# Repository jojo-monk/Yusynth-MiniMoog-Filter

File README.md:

# Yusynth-MiniMoog-Filter
Adaptation du Yusynth [MiniMoog Filter](http://yusynth.net/Modular/index_en.html) au format Eurorack

testé et fonctionnel.

petit défaut esthetique : sérigraphie un peu trop petite et trop proche des boutons.

[Build document](https://htmlpreview.github.io/?https://github.com/jojo-monk/Yusynth-MiniMoog-Filter/blob/main/ibom.html)

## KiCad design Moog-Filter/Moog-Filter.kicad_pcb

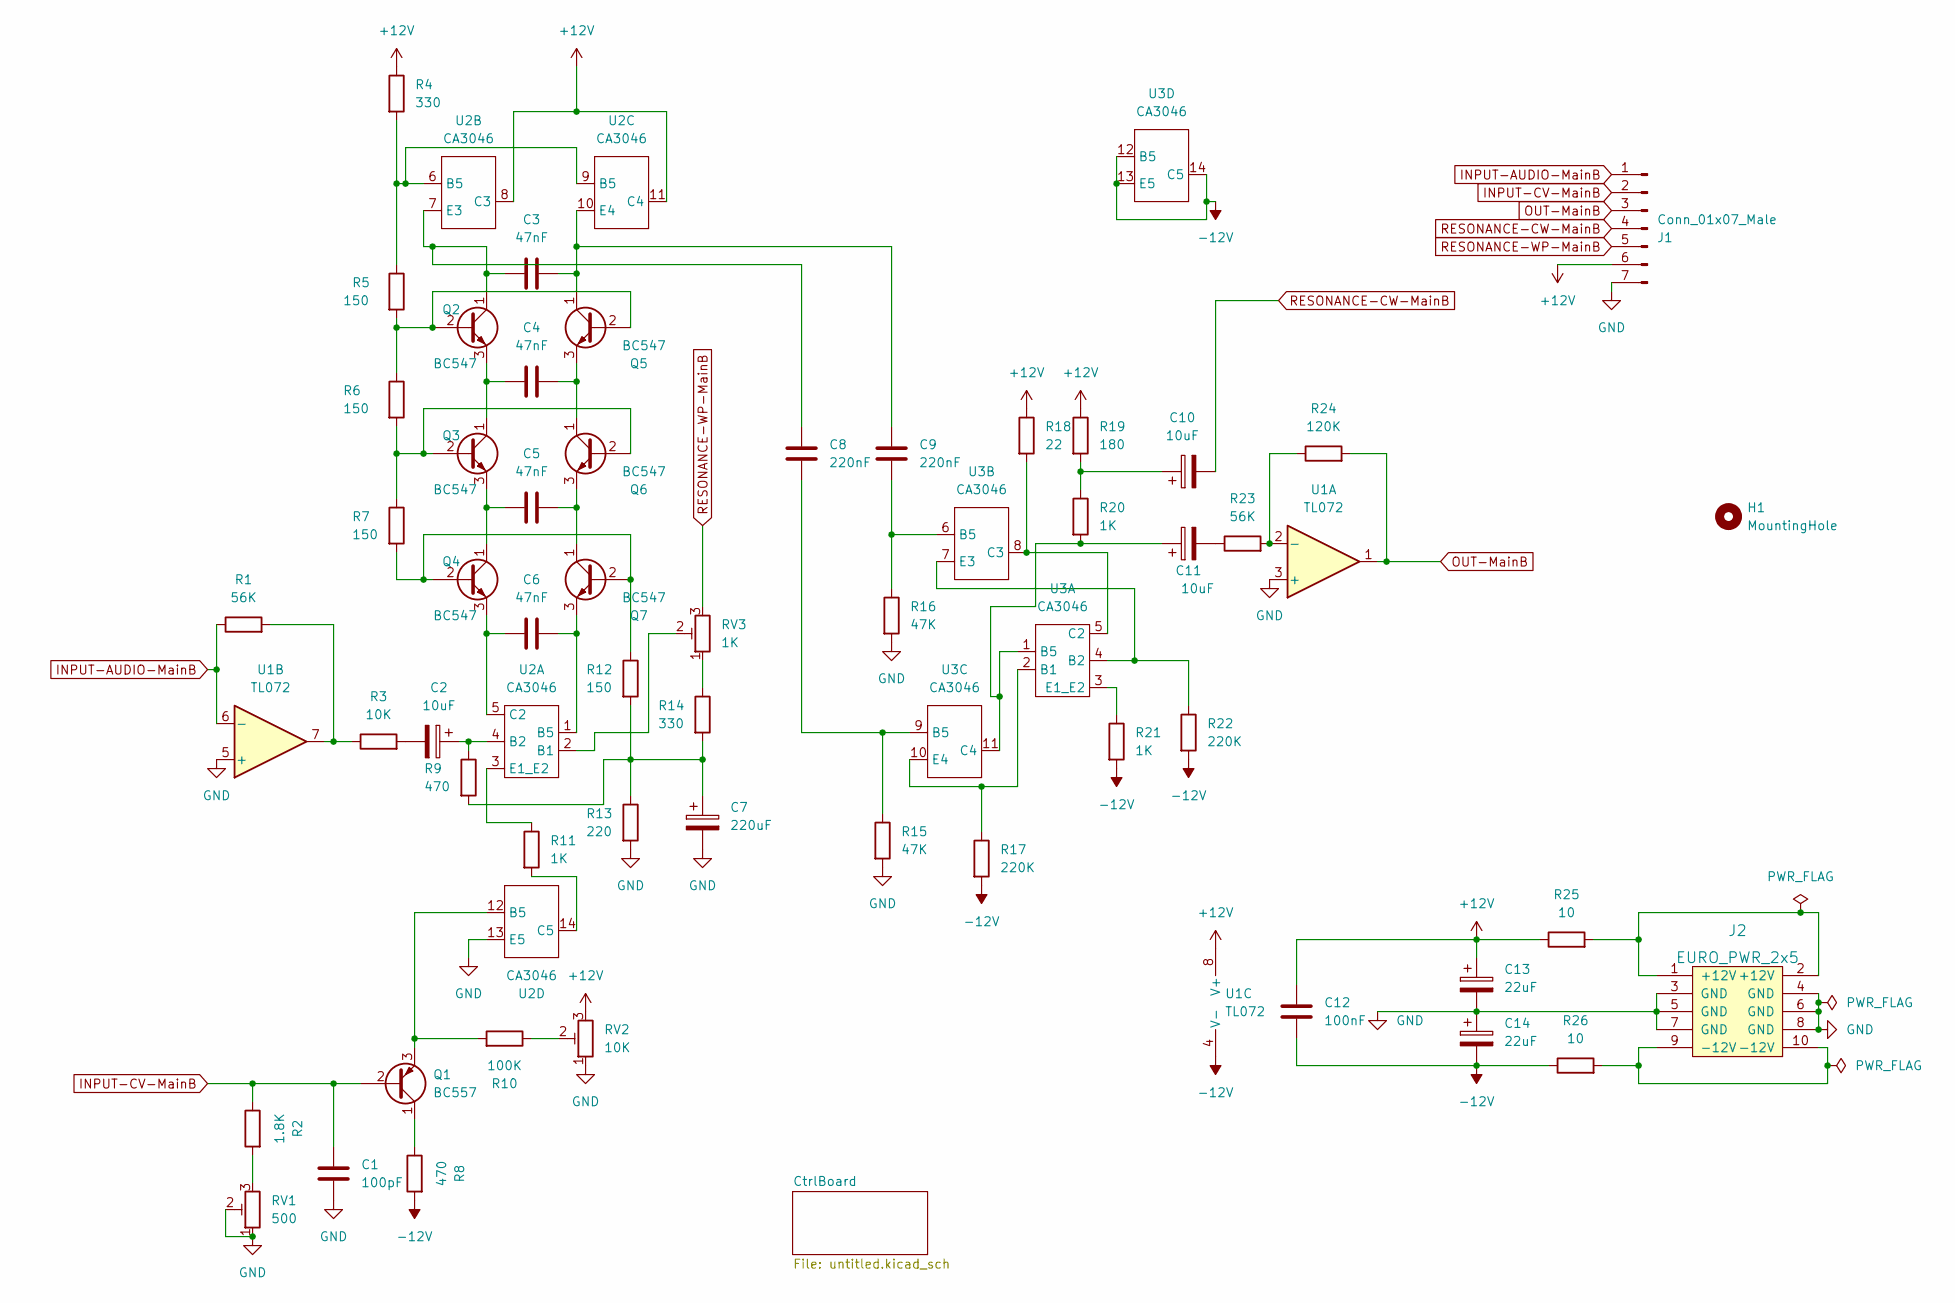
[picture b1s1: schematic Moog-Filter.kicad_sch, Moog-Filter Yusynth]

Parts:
C1: 100pF; C_Rect_L7.0mm_W3.5mm_P5.00mm
C2, C10, C11: 10uF; CP_Radial_D5.0mm_P2.00mm
C3, C4, C5, C6: 47nF; C_Rect_L7.0mm_W3.5mm_P5.00mm
C7: 220uF; CP_Radial_D8.0mm_P3.50mm
C8, C9: 220nF; C_Rect_L7.0mm_W3.5mm_P5.00mm
C12: 100nF; C_Rect_L7.0mm_W3.5mm_P5.00mm
C13, C14: 22uF; CP_Radial_D5.0mm_P2.00mm
H1: MountingHole; MountingHole_3.2mm_M3
J1: Conn_01x07_Male; PinHeader_1x07_P2.54mm_Vertical
J2: EURO_PWR_2x5; Eurorack_power_header
Q1: BC557; TO-92_HandSolder
Q2, Q3, Q4, Q5, Q6, Q7: BC547; TO-92_HandSolder
R1, R23: 56K; R_Axial_DIN0207_L6.3mm_D2.5mm_P2.54mm_Vertical
R2: 1.8K; R_Axial_DIN0207_L6.3mm_D2.5mm_P2.54mm_Vertical
R3: 10K; R_Axial_DIN0207_L6.3mm_D2.5mm_P2.54mm_Vertical
R4, R14: 330; R_Axial_DIN0207_L6.3mm_D2.5mm_P2.54mm_Vertical
R5, R6, R7, R12: 150; R_Axial_DIN0207_L6.3mm_D2.5mm_P2.54mm_Vertical
R8, R9: 470; R_Axial_DIN0207_L6.3mm_D2.5mm_P2.54mm_Vertical
R10: 100K; R_Axial_DIN0207_L6.3mm_D2.5mm_P2.54mm_Vertical
R11, R20, R21: 1K; R_Axial_DIN0207_L6.3mm_D2.5mm_P2.54mm_Vertical
R13: 220; R_Axial_DIN0207_L6.3mm_D2.5mm_P2.54mm_Vertical
R15, R16: 47K; R_Axial_DIN0207_L6.3mm_D2.5mm_P2.54mm_Vertical
R17, R22: 220K; R_Axial_DIN0207_L6.3mm_D2.5mm_P2.54mm_Vertical
R18: 22; R_Axial_DIN0207_L6.3mm_D2.5mm_P2.54mm_Vertical
R19: 180; R_Axial_DIN0207_L6.3mm_D2.5mm_P2.54mm_Vertical
R24: 120K; R_Axial_DIN0207_L6.3mm_D2.5mm_P2.54mm_Vertical
R25, R26: 10; R_Axial_DIN0207_L6.3mm_D2.5mm_P2.54mm_Vertical
RV1: 500; Potentiometer_Bourns_3296W_Vertical
RV2: 10K; Potentiometer_Bourns_3296W_Vertical
RV3: 1K; Potentiometer_Bourns_3296W_Vertical
U1: TL072; DIP-8_W7.62mm_LongPads
U2, U3: CA3046; DIP-14_W7.62mm_LongPads

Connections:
+12V: C12.1, C13.1, J1.6, R4.1, R18.1, R19.1, R25.1, RV2.3, U1.8 (V+), U2.8 (C3), U2.11 (C4); also elsewhere on the board
-12V: C12.2, C14.2, R8.2, R17.2, R21.2, R22.2, R26.1, U1.4 (V-), U3.12 (B5), U3.13 (E5), U3.14 (C5)
GND: C1.2, C7.2, C13.2, C14.1, J1.7, J2.3 (GND), J2.4 (GND), J2.5 (GND), J2.6 (GND), J2.7 (GND), J2.8 (GND), R13.2, R15.2, R16.2, RV1.1, RV1.2, RV2.1, U1.3 (+), U1.5 (+), U2.13 (E5); also elsewhere on the board
INPUT-AUDIO-MainB: J1.1, R1.1, U1.6 (-)
INPUT-CV-MainB: C1.1, J1.2, Q1.2 (B), R2.1
unnamed: C2.1, R9.1, U2.4 (B2)
unnamed: C2.2, R3.2
unnamed: C3.1, C8.1, Q2.1 (C), U2.7 (E3)
unnamed: C3.2, C9.1, Q5.1 (C), U2.10 (E4)
unnamed: C4.1, Q2.3 (E), Q3.1 (C)
unnamed: C4.2, Q5.3 (E), Q6.1 (C)
unnamed: C5.1, Q3.3 (E), Q4.1 (C)
unnamed: C5.2, Q6.3 (E), Q7.1 (C)
unnamed: C6.1, Q4.3 (E), U2.5 (C2)
unnamed: C6.2, Q7.3 (E), U2.1 (B5)
unnamed: C7.1, R9.2, R12.2, R13.1, R14.2
unnamed: C8.2, R15.1, U3.9 (B5)
unnamed: C9.2, R16.1, U3.6 (B5)
unnamed: C10.1, R19.2, R20.1
unnamed: C11.1, R20.2, U3.1 (B5), U3.11 (C4)
unnamed: C11.2, R23.1
unnamed: J2.1 (+12V), J2.2 (+12V), R25.2
unnamed: J2.9 (-12V), J2.10 (-12V), R26.2
unnamed: Q1.1 (C), R8.1
unnamed: Q1.3 (E), R10.2, U2.12 (B5)
unnamed: Q2.2 (B), Q5.2 (B), R5.2, R6.1
unnamed: Q3.2 (B), Q6.2 (B), R6.2, R7.1
unnamed: Q4.2 (B), Q7.2 (B), R7.2, R12.1
unnamed: R1.2, R3.1, U1.7
unnamed: R2.2, RV1.3
unnamed: R4.2, R5.1, U2.6 (B5), U2.9 (B5)
unnamed: R10.1, RV2.2
unnamed: R11.1, U2.3 (E1_E2)
unnamed: R11.2, U2.14 (C5)
unnamed: R14.1, RV3.1
unnamed: R17.1, U3.2 (B1), U3.10 (E4)
unnamed: R18.2, U3.5 (C2), U3.8 (C3)
unnamed: R21.1, U3.3 (E1_E2)
unnamed: R22.1, U3.4 (B2), U3.7 (E3)
unnamed: R23.2, R24.1, U1.2 (-)
unnamed: RV3.2, U2.2 (B1)
OUT-MainB: J1.3, R24.2, U1.1
RESONANCE-CW-MainB: C10.2, J1.4
RESONANCE-WP-MainB: J1.5, RV3.3

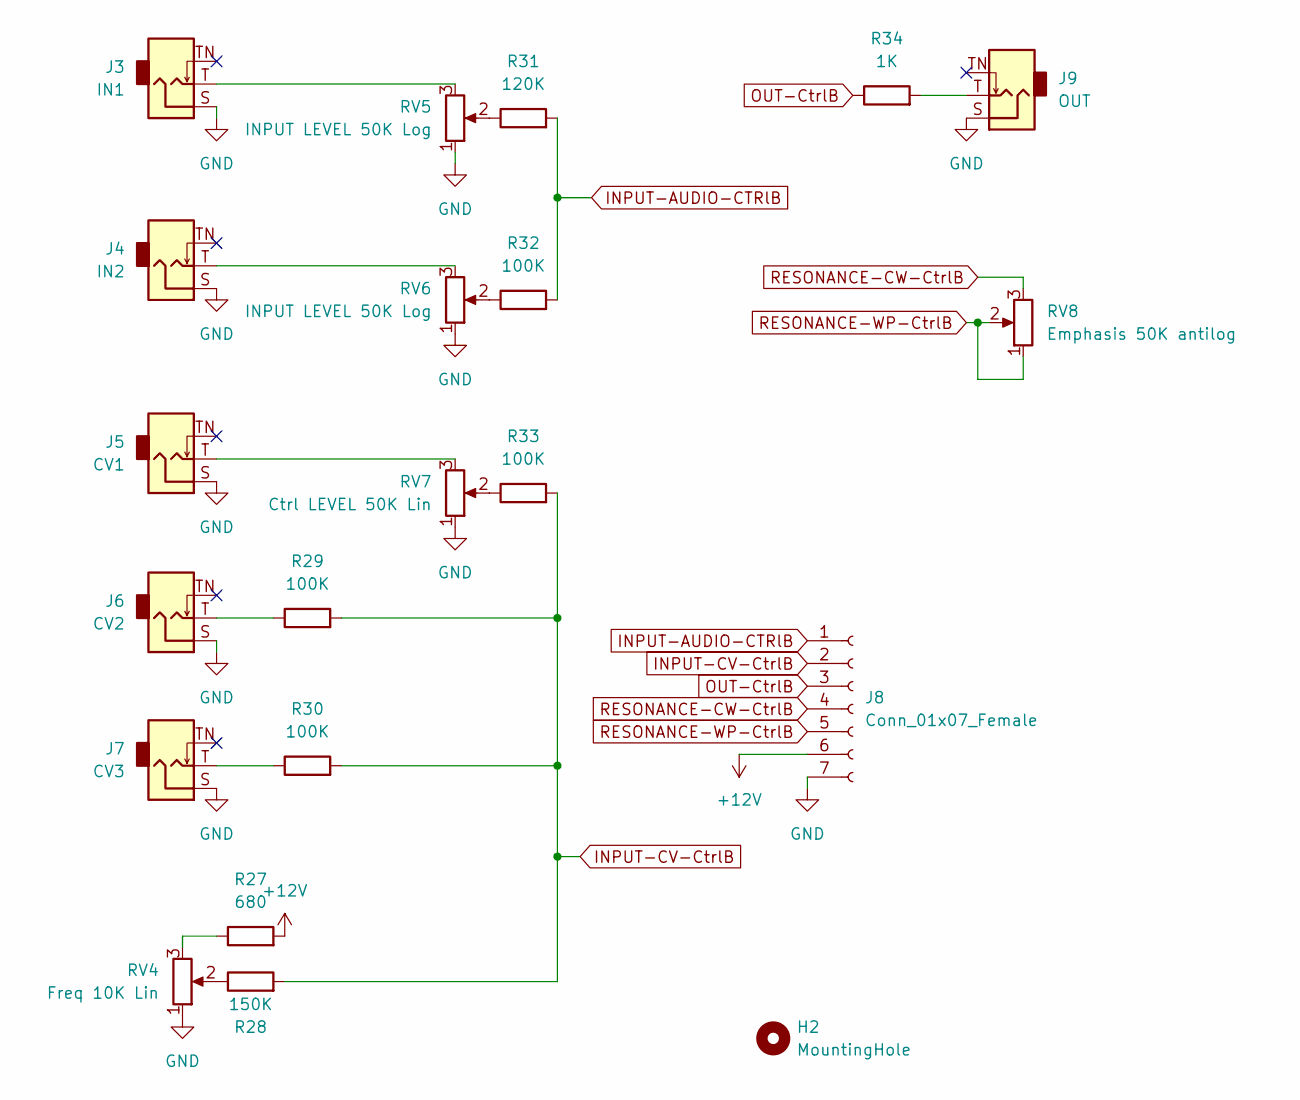
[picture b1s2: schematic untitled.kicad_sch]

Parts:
H2: MountingHole; MountingHole_3.2mm_M3
J3: IN1; Jack_3.5mm_QingPu_WQP-PJ398SM_Vertical
J4: IN2; Jack_3.5mm_QingPu_WQP-PJ398SM_Vertical
J5: CV1; Jack_3.5mm_QingPu_WQP-PJ398SM_Vertical
J6: CV2; Jack_3.5mm_QingPu_WQP-PJ398SM_Vertical
J7: CV3; Jack_3.5mm_QingPu_WQP-PJ398SM_Vertical
J8: Conn_01x07_Female; PinHeader_1x07_P2.54mm_Vertical
J9: OUT; Jack_3.5mm_QingPu_WQP-PJ398SM_Vertical
R27: 680; R_Axial_DIN0207_L6.3mm_D2.5mm_P2.54mm_Vertical
R28: 150K; R_Axial_DIN0207_L6.3mm_D2.5mm_P2.54mm_Vertical
R29, R30, R32, R33: 100K; R_Axial_DIN0207_L6.3mm_D2.5mm_P2.54mm_Vertical
R31: 120K; R_Axial_DIN0207_L6.3mm_D2.5mm_P2.54mm_Vertical
R34: 1K; R_Axial_DIN0207_L6.3mm_D2.5mm_P2.54mm_Vertical
RV4: Freq 10K Lin; Potentiometer_Alpha_RD901F-40-00D_Single_Vertical
RV5, RV6: INPUT LEVEL 50K Log; Potentiometer_Alpha_RD901F-40-00D_Single_Vertical
RV7: Ctrl LEVEL 50K Lin; Potentiometer_Alpha_RD901F-40-00D_Single_Vertical
RV8: Emphasis 50K antilog; Potentiometer_Alpha_RD901F-40-00D_Single_Vertical

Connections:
+12V: J8.6, R27.2; also elsewhere on the board
GND: J3.S, J4.S, J5.S, J6.S, J7.S, J8.7, J9.S, RV4.1, RV5.1, RV6.1, RV7.1; also elsewhere on the board
INPUT-AUDIO-CTRlB: J8.1, R31.2, R32.2
INPUT-CV-CtrlB: J8.2, R28.2, R29.2, R30.2, R33.2
unnamed: J3.T, RV5.3
unnamed: J4.T, RV6.3
unnamed: J5.T, RV7.3
unnamed: J6.T, R29.1
unnamed: J7.T, R30.1
unnamed: J9.T, R34.2
unnamed: R27.1, RV4.3
unnamed: R28.1, RV4.2
unnamed: R31.1, RV5.2
unnamed: R32.1, RV6.2
unnamed: R33.1, RV7.2
OUT-CtrlB: J8.3, R34.1
RESONANCE-CW-CtrlB: J8.4, RV8.3
RESONANCE-WP-CtrlB: J8.5, RV8.1, RV8.2

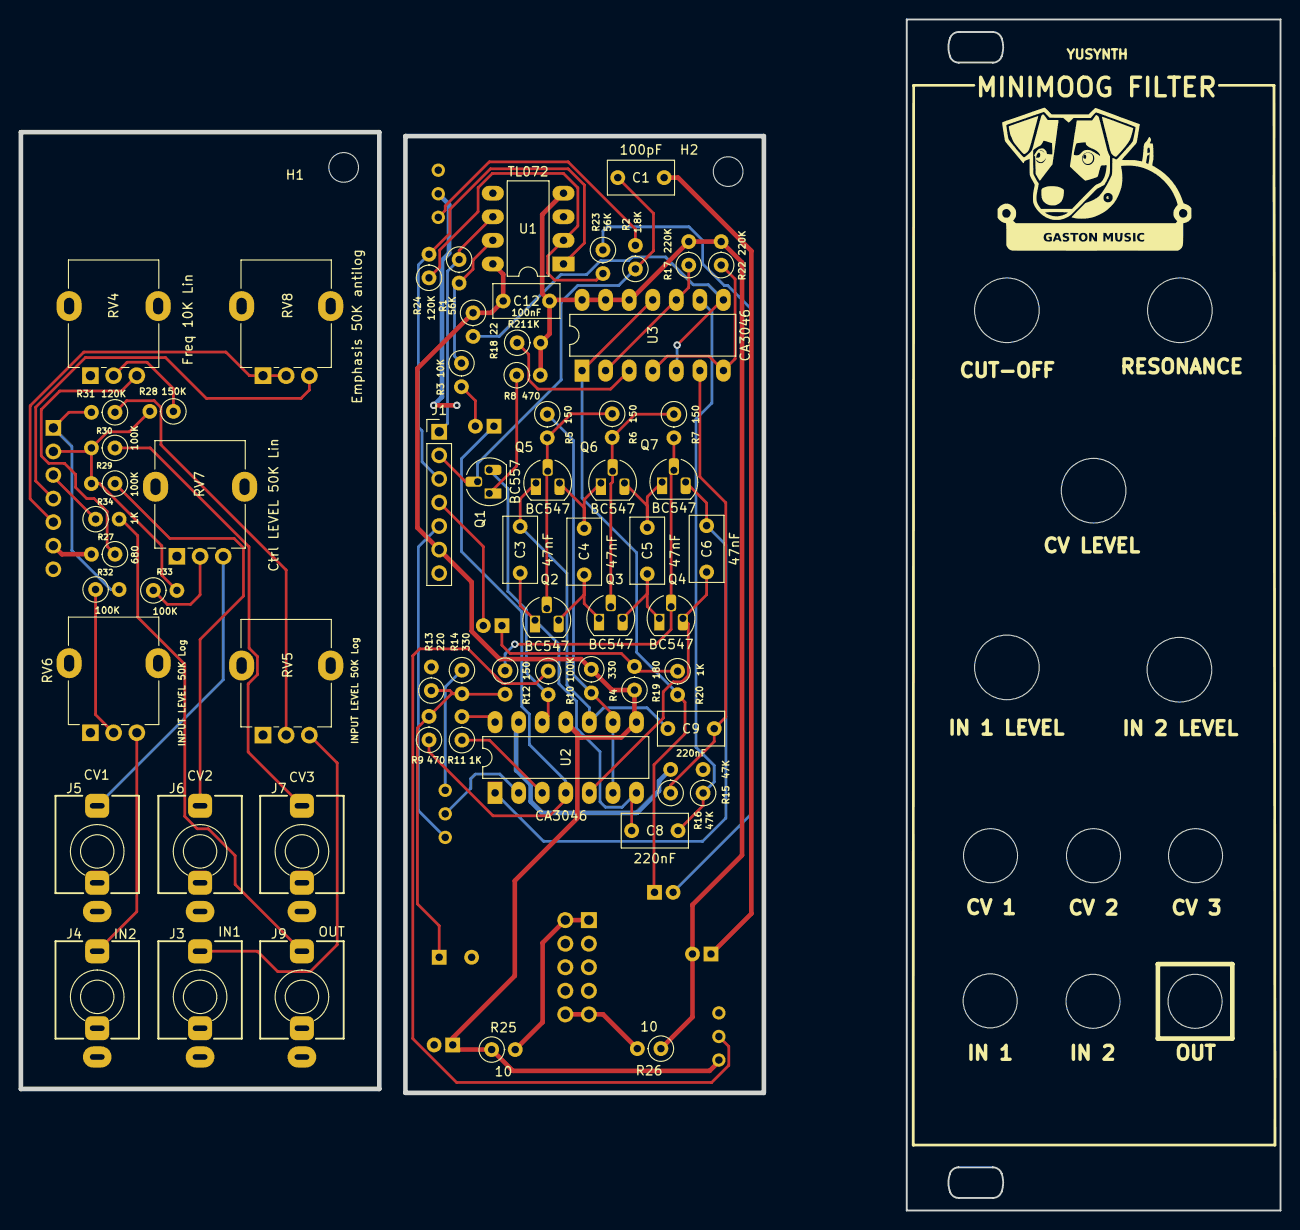
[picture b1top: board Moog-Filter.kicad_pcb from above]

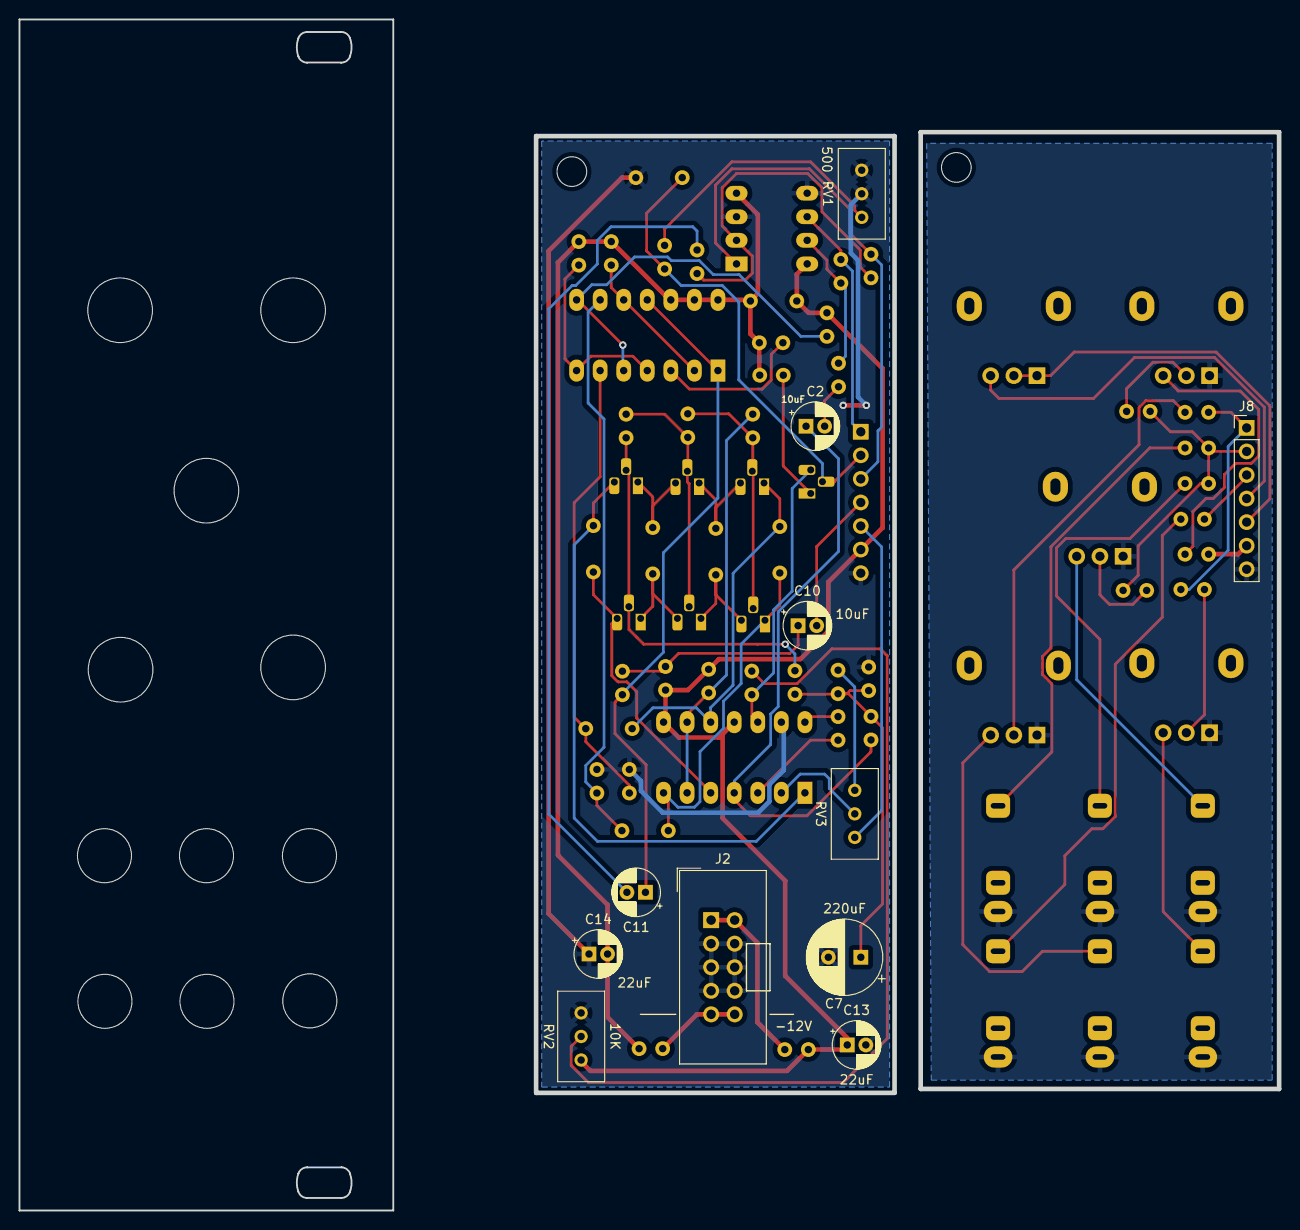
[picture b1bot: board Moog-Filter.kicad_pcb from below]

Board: 2 copper layers, 135.7 x 128.1 mm, 77 parts (11 on the bottom side), 60 nets.

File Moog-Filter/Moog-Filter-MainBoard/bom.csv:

Designator,Footprint,Quantity,Value,LCSC Part #
C1,C_Rect_L7.0mm_W3.5mm_P5.00mm,1,100pF,
"C10, C11, C2",CP_Radial_D5.0mm_P2.00mm,3,10uF,
C12,C_Rect_L7.0mm_W3.5mm_P5.00mm,1,100nF,
"C13, C14",CP_Radial_D5.0mm_P2.00mm,2,22uF,
"C3, C4, C5, C6",C_Rect_L7.0mm_W3.5mm_P5.00mm,4,47nF,
C7,CP_Radial_D8.0mm_P3.50mm,1,220uF,
"C8, C9",C_Rect_L7.0mm_W3.5mm_P5.00mm,2,220nF,
H2,MountingHole_3.2mm_M3,1,MountingHole,
J1,PinHeader_1x07_P2.54mm_Vertical,1,Conn_01x07_Male,
J2,Eurorack_power_header,1,EURO_PWR_2x5,
Q1,TO-92_HandSolder,1,BC557,
"Q2, Q3, Q4, Q5, Q6, Q7",TO-92_HandSolder,6,BC547,
"R1, R23",R_Axial_DIN0207_L6.3mm_D2.5mm_P2.54mm_Vertical,2,56K,
R10,R_Axial_DIN0207_L6.3mm_D2.5mm_P2.54mm_Vertical,1,100K,
"R11, R20, R21",R_Axial_DIN0207_L6.3mm_D2.5mm_P2.54mm_Vertical,3,1K,
"R12, R5, R6, R7",R_Axial_DIN0207_L6.3mm_D2.5mm_P2.54mm_Vertical,4,150,
R13,R_Axial_DIN0207_L6.3mm_D2.5mm_P2.54mm_Vertical,1,220,
"R14, R4",R_Axial_DIN0207_L6.3mm_D2.5mm_P2.54mm_Vertical,2,330,
"R15, R16",R_Axial_DIN0207_L6.3mm_D2.5mm_P2.54mm_Vertical,2,47K,
"R17, R22",R_Axial_DIN0207_L6.3mm_D2.5mm_P2.54mm_Vertical,2,220K,
R18,R_Axial_DIN0207_L6.3mm_D2.5mm_P2.54mm_Vertical,1,22,
R19,R_Axial_DIN0207_L6.3mm_D2.5mm_P2.54mm_Vertical,1,180,
R2,R_Axial_DIN0207_L6.3mm_D2.5mm_P2.54mm_Vertical,1,1.8K,
R24,R_Axial_DIN0207_L6.3mm_D2.5mm_P2.54mm_Vertical,1,120K,
"R25, R26",R_Axial_DIN0207_L6.3mm_D2.5mm_P2.54mm_Vertical,2,10,
R3,R_Axial_DIN0207_L6.3mm_D2.5mm_P2.54mm_Vertical,1,10K,
"R8, R9",R_Axial_DIN0207_L6.3mm_D2.5mm_P2.54mm_Vertical,2,470,
RV1,Potentiometer_Bourns_3296W_Vertical,1,500,
RV2,Potentiometer_Bourns_3296W_Vertical,1,10K,
RV3,Potentiometer_Bourns_3296W_Vertical,1,1K,
U1,DIP-8_W7.62mm_LongPads,1,TL072,
"U2, U3",DIP-14_W7.62mm_LongPads,2,CA3046,

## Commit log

2023-05-03 eurorack version
2023-05-03 déplacement ibom
2023-05-29 ajout images
